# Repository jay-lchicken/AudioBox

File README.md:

# AudioBox

## Introduction
I have always wanted to be able to play sound effects from an actual device where I can just smack the button and the effect will play without having to use my phone.

Then, I thought, what if I created a device that is just a button

From there, I thought how can I make this project unique.

This project is powered by a Seeed Xiao RP2040 because it is affordable and has a large flash size. It is tiny too.

Next, I added 3W 8Ω speakers that can go up to 110DB!! That is to ensure that the sound effect can be heard even in a loudroom

Instead of using traditional buttons, I decided to go with limit switches so that the user can experience the satisfying click sound when the button is pressed

To reduce static noise, I added a decoupling and a bypass capacitor to the circuit. This will help to ensure that there is no static noise

## Images

## BOM
# Bill of Materials (BOM)

| Item | Qty | Unit Cost (USD) | Total Cost (USD) |
|------|-----|-----------------|------------------|
| PCB + PCBA | 1   | 37.02 | 37.02            |
| Speaker | 1   | 2.30 | 2.30             |
| SS-5GL | 1   | 1.60 | 1.60             |
| Seeed XIAO RP2040 | 1   | 3.71 | 3.71             |
| **Total** |     |  | **44.63**        |

## Future Plans

I plan on creating a website once the hardware is done to talk to the RP2040, to download and install new audio

This makes it a well-polished product, rather than having to open up the code just to change the audio

If not for this feature, I would have just used a normal pcb audio player and no need for the rp2040

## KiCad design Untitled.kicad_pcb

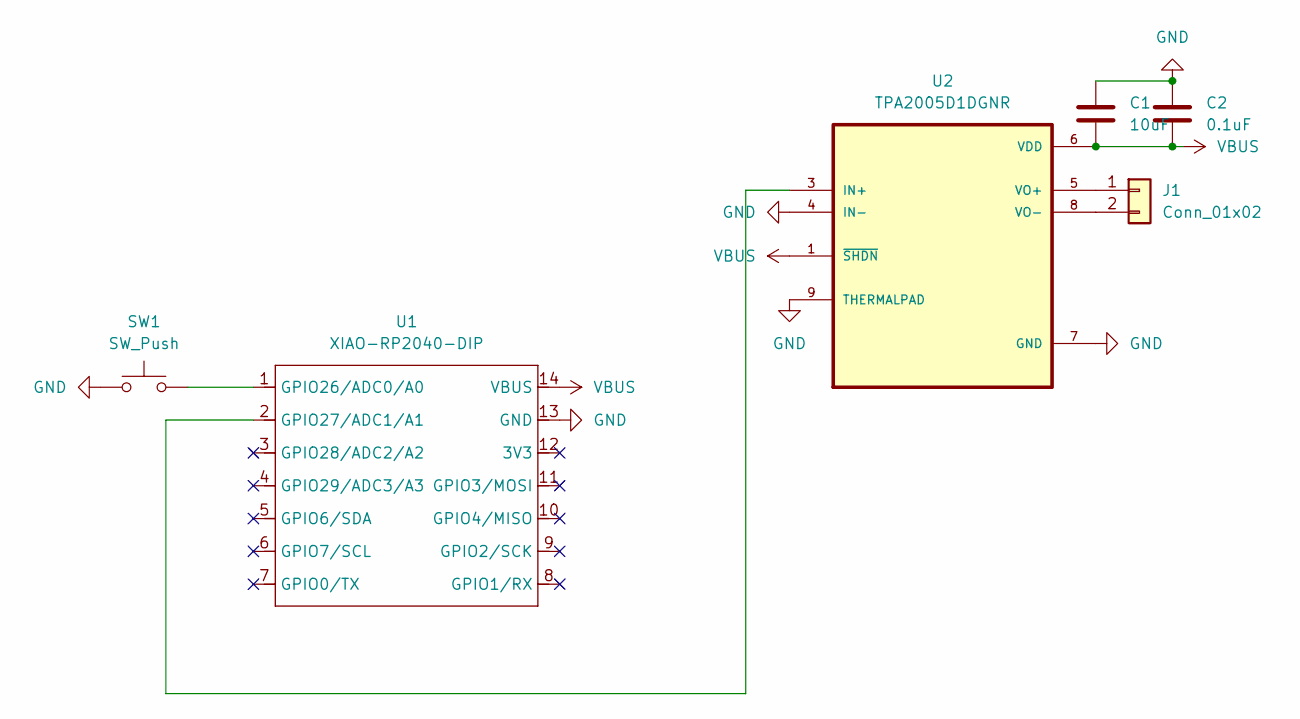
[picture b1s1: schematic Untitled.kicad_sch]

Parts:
C1: 10uF; C_0805_2012Metric; LCSC C1713
C2: 0.1uF; C_0402_1005Metric; LCSC C1525
J1: Conn_01x02; TerminalBlock_Phoenix_PT-1,5-2-3.5-H_1x02_P3.50mm_Horizontal; LCSC C3703
SW1: SW_Push; TerminalBlock_Phoenix_PT-1,5-2-3.5-H_1x02_P3.50mm_Horizontal; LCSC C3703
U1: XIAO-RP2040-DIP
U2: TPA2005D1DGNR; SOP65P490X110-9N; LCSC C27396

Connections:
GND: C1.1, C2.1, SW1.1, U1.13 (GND), U2.4 (IN-), U2.7 (GND), U2.9 (THERMALPAD)
unnamed: J1.1, U2.5 (VO+)
unnamed: J1.2, U2.8 (VO-)
unnamed: SW1.2, U1.1 (GPIO26/ADC0/A0)
unnamed: U1.2 (GPIO27/ADC1/A1), U2.3 (IN+)
VBUS: C1.2, C2.2, U1.14 (VBUS), U2.1 (~SHDN), U2.6 (VDD)

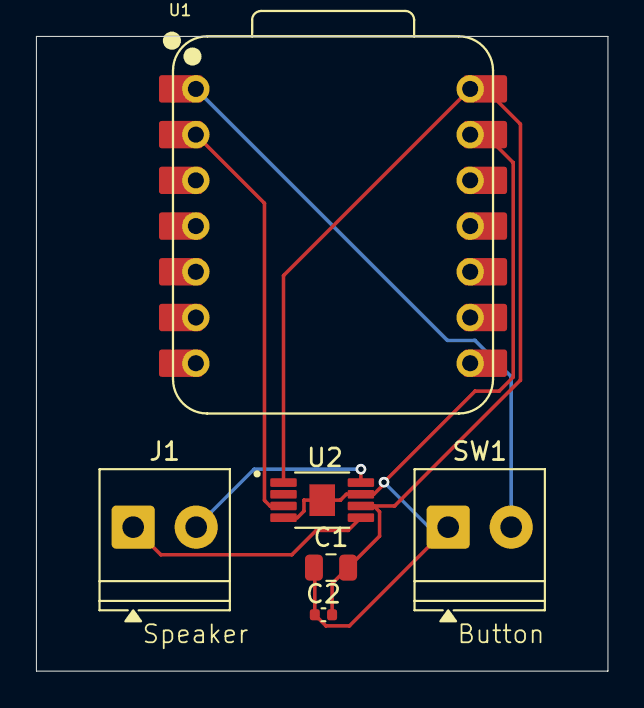
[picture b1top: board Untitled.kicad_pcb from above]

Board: 2 copper layers, 31.8 x 35.3 mm, 6 parts (0 on the bottom side), 6 nets.

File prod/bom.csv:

Designator,Footprint,Quantity,Value,LCSC Part #
C1,0805,1,10uF,
C2,0402,1,0.1uF,
J1,"TerminalBlock_Phoenix_PT-1,5-2-3.5-H_1x02_P3.50mm_Horizontal",1,Conn_01x02,
SW1,"TerminalBlock_Phoenix_PT-1,5-2-3.5-H_1x02_P3.50mm_Horizontal",1,SW_Push,
U1,XIAO-RP2040-DIP,1,XIAO-RP2040-DIP,
U2,SOP65P490X110-9N,1,TPA2005D1DGNR,

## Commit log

2026-06-12 firmware v1
2026-06-13 everything
2026-06-13 added readme
2026-06-13 changed to opensourcecode instead of the original wavplayer code
2026-06-13 modified bom to remove spares
2026-06-15 added schematics and pcb
